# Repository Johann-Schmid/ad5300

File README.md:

# ad5300
 Example Project for the AD5300

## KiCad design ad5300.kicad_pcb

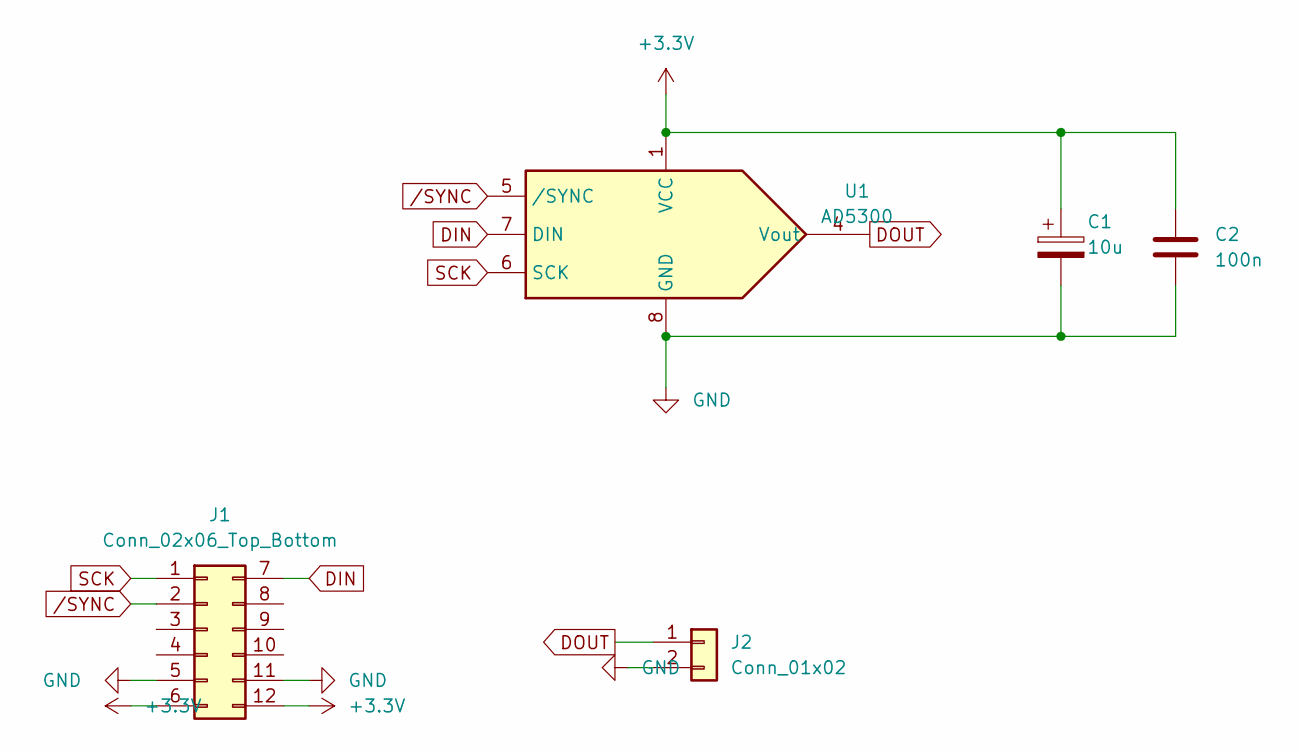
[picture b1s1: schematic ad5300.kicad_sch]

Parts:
C1: 10u; CP_Radial_D6.3mm_P2.50mm
C2: 100n; C_Rect_L7.2mm_W2.5mm_P5.00mm_FKS2_FKP2_MKS2_MKP2
J1: Conn_02x06_Top_Bottom; PinHeader_2x06_P2.54mm_Horizontal
J2: Conn_01x02; PinHeader_1x02_P2.54mm_Vertical
U1: AD5300; MSOP-8_3x3mm_P0.65mm

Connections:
+3.3V: C1.1, C2.1, J1.6, J1.12, U1.1 (VCC)
DIN: J1.7, U1.7 (DIN)
DOUT: J2.1, U1.4 (Vout)
GND: C1.2, C2.2, J1.5, J1.11, J2.2, U1.8 (GND)
SCK: J1.1, U1.6 (SCK)
/SYNC: J1.2, U1.5 (/SYNC)

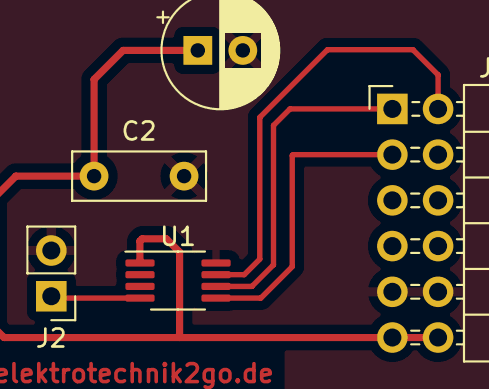
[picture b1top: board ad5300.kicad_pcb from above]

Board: 2 copper layers, 5 parts (0 on the bottom side), 6 nets.
